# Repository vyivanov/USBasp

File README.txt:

FUSES SETTINGS
low:  0xEF
high: 0xC0

LOCKBITS SETTINGS
0x2F

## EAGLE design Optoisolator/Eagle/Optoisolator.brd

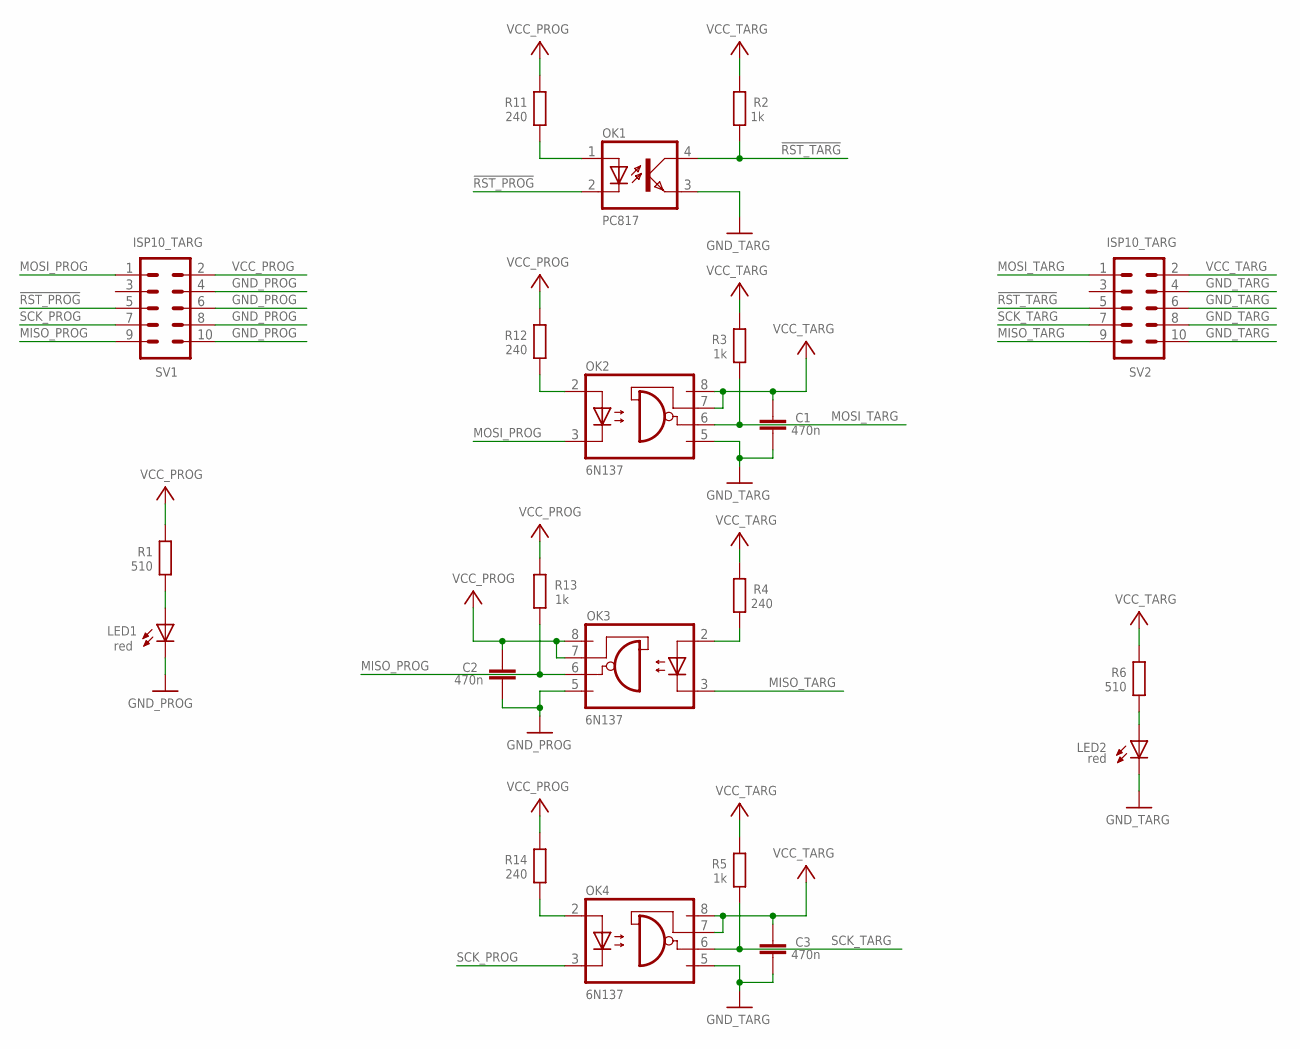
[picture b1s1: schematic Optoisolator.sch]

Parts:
C1, C2, C3: 470n; C1206
LED1, LED2: red; LED3MM
OK1: PC817; DIL04
OK2, OK3, OK4: 6N137; DIL08
R1, R6: 510; R1206
R2, R3, R5, R13: 1k; R1206
R4, R11, R12, R14: 240; R1206
SV1, SV2: ISP10_TARG; ML10

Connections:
!RST_PROG: OK1.2 (C), SV1.5
!RST_TARG: OK1.4 (COL), R2.1, SV2.5
GND_PROG: C2.2, LED1.K (C), OK3.5 (GND), SV1.4, SV1.6, SV1.8, SV1.10
GND_TARG: C1.2, C3.2, LED2.K (C), OK1.3 (EMIT), OK2.5 (GND), OK4.5 (GND), SV2.4, SV2.6, SV2.8, SV2.10
MISO_PROG: OK3.6 (VO), R13.1, SV1.9
MISO_TARG: OK3.3 (C), SV2.9
MOSI_PROG: OK2.3 (C), SV1.1
MOSI_TARG: OK2.6 (VO), R3.1, SV2.1
unnamed: OK1.1 (A), R11.1
unnamed: OK2.2 (A), R12.1
unnamed: OK4.2 (A), R14.1
unnamed: LED2.A, R6.1
unnamed: LED1.A, R1.1
unnamed: OK3.2 (A), R4.1
SCK_PROG: OK4.3 (C), SV1.7
SCK_TARG: OK4.6 (VO), R5.1, SV2.7
VCC_PROG: C2.1, OK3.7 (VE), OK3.8 (VCC), R1.2, R11.2, R12.2, R13.2, R14.2, SV1.2
VCC_TARG: C1.1, C3.1, OK2.7 (VE), OK2.8 (VCC), OK4.7 (VE), OK4.8 (VCC), R2.2, R3.2, R4.2, R5.2, R6.2, SV2.2

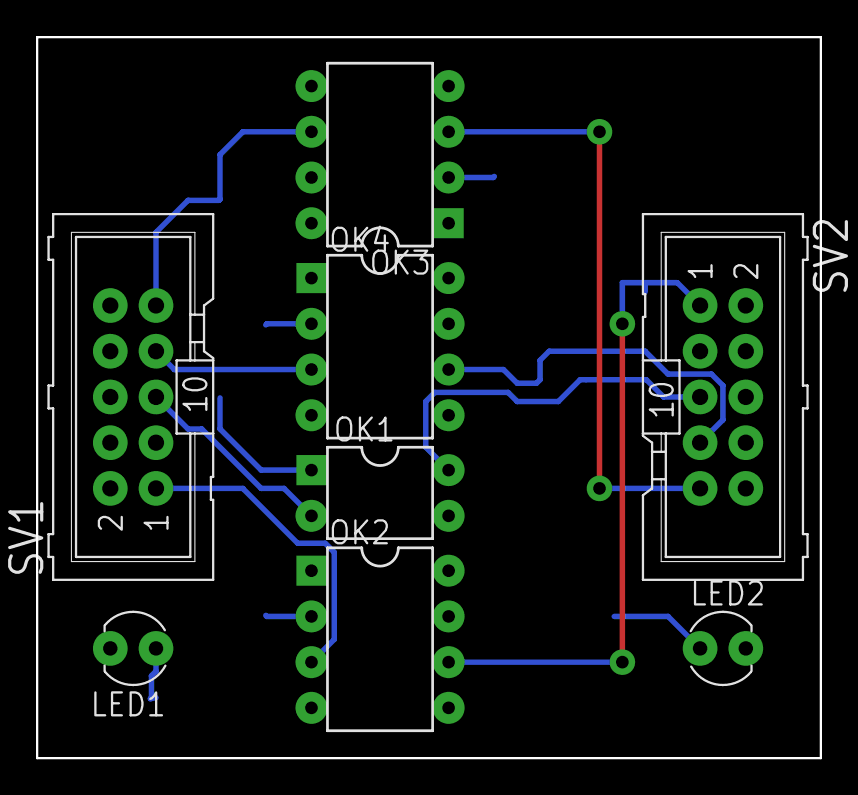
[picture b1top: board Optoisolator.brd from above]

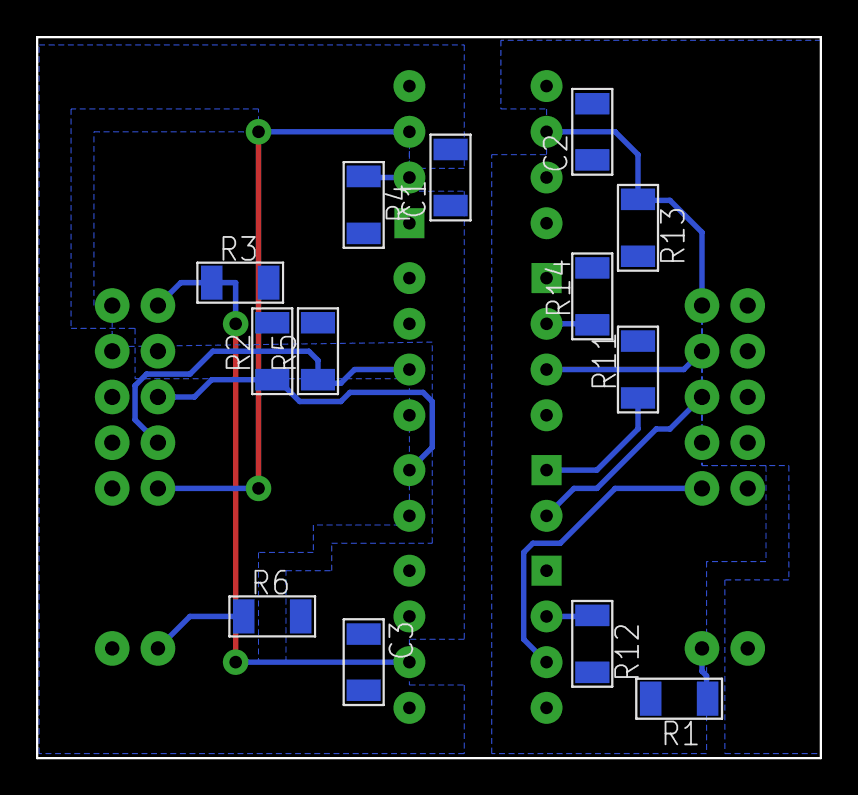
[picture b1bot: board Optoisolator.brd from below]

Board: 2 copper layers, 43.5 x 40.1 mm, 21 parts (13 on the bottom side), 18 nets.

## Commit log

2012-02-25 Init
2012-07-20 Minor changes
2012-08-13 Sketched layout of optoisolator
2012-08-14 Routed right-hand side of optoisolator
2012-08-14 Routed optoisolator
2012-08-15 Replaced through-hole bypass capacitors with smd one
